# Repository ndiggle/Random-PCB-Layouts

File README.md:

# Random-PCB-Layouts

## Objective
I've uploaded some PCB layouts that I've done in Eagle and KiCad over the past few months. The majority of these layouts were done for pedagogical purposes, but feel free to use any of the designs for alternate uses.

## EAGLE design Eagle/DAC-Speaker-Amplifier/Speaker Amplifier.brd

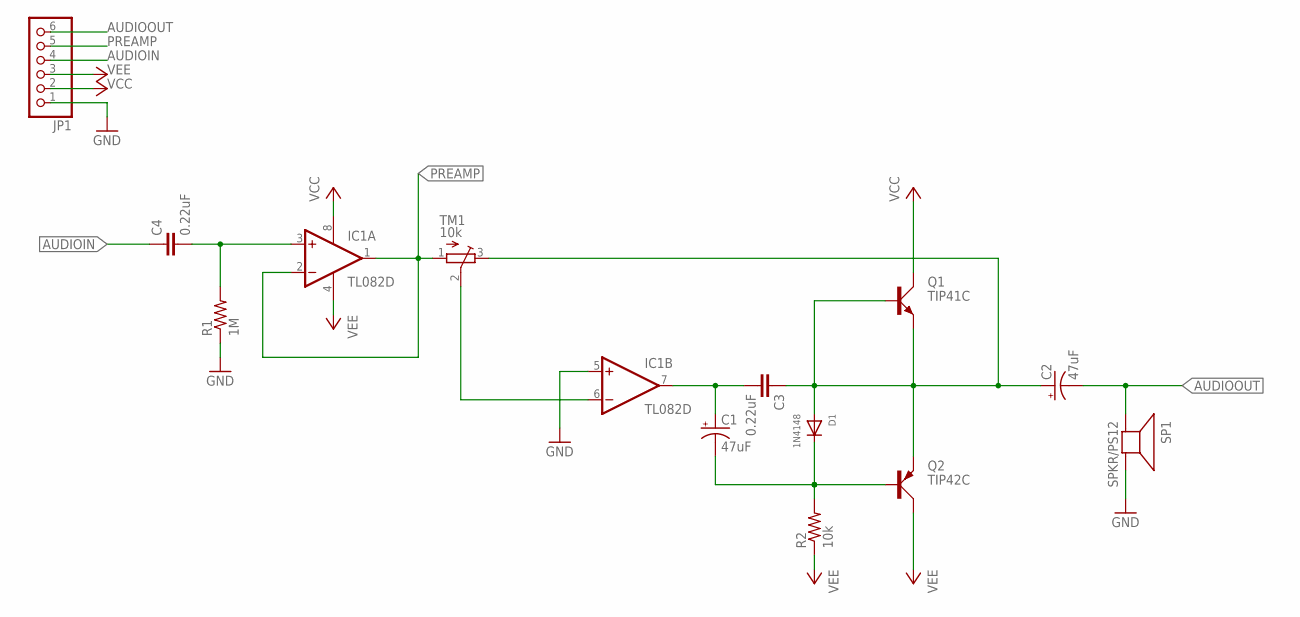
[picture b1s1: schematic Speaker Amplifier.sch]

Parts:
C1, C2: 47uF; 153CLV-0810
C3, C4: 0.22uF; C0805
D1: 1N4148; SOD-323F
IC1: TL082D; SO08
JP1: PINHD-1X6-3.5MM; 1X06-3.5MM
Q1: TIP41C; TO220AV
Q2: TIP42C; TO220AV
R1: 1M; R0805
R2: 10k; R0805
SP1: SPKR/PS12; PS12
TM1: 10k; TC33X

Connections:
AUDIOIN: C4.1, JP1.4
AUDIOOUT: C2.-, JP1.6, SP1.P$1 (+)
GND: IC1.5 (+IN), JP1.1, R1.1, SP1.P$2 (-)
unnamed: C4.2, IC1.3 (+IN), R1.2
unnamed: C1.-, D1.C, Q2.B, R2.2
unnamed: C1.+, C3.2, IC1.7 (OUT)
unnamed: C2.+, C3.1, D1.A, Q1.B, Q1.E, Q2.E, TM1.3 (E)
unnamed: IC1.6 (-IN), TM1.2 (S)
PREAMP: IC1.1 (OUT), IC1.2 (-IN), JP1.5, TM1.1 (A)
VCC: IC1.4 (V-), IC1.8 (V+), JP1.2, JP1.3, Q1.C, Q2.C, R2.1

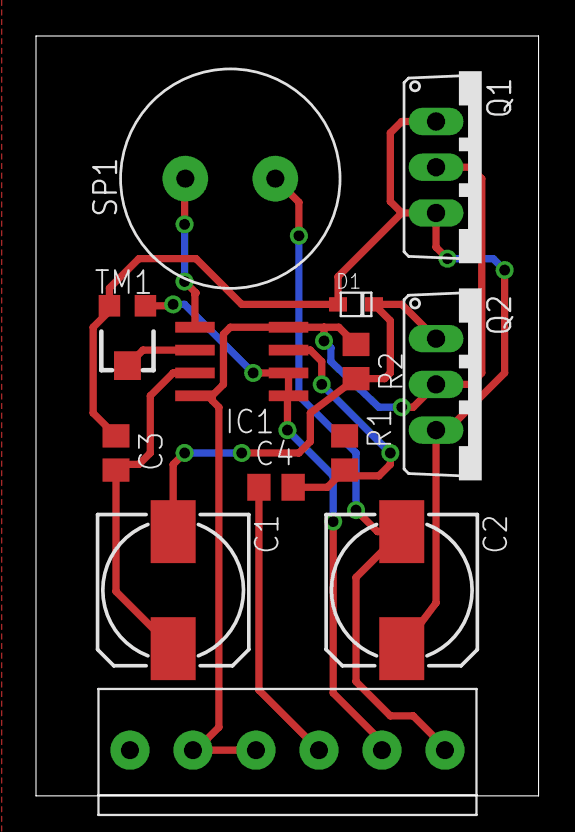
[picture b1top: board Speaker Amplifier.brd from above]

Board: 2 copper layers, 27.9 x 42.2 mm, 13 parts (0 on the bottom side), 10 nets.

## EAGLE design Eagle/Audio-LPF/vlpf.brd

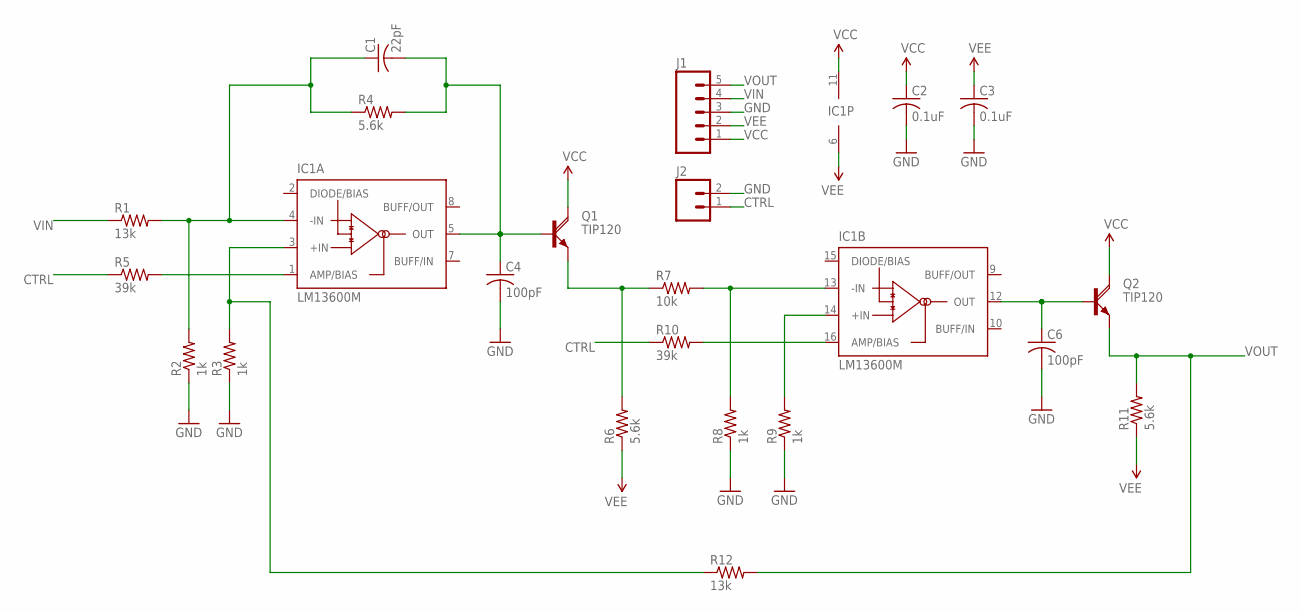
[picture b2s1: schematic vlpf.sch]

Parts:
C1: 22pF; C0504
C2, C3: 0.1uF; C0504
C4, C6: 100pF; C0504
IC1: LM13600M; SO16
J1: M05PTH; 1X05
J2: M02PTH; 1X02
Q1, Q2: TIP120; TO220AH
R1, R12: 13k; R0402
R2, R3, R8, R9: 1k; R0402
R4, R6, R11: 5.6k; R0402
R5, R10: 39k; R0402
R7: 10k; R0402

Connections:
CTRL: J2.1, R5.1, R10.1
GND: C2.2, C3.2, C4.2, C6.2, J1.3, J2.2, R2.1, R3.1, R8.1, R9.1
unnamed: C1.1, IC1.4 (-IN), R1.2, R2.2, R4.1
unnamed: IC1.3 (+IN), R3.2, R12.1
unnamed: C1.2, C4.1, IC1.5 (OUT), Q1.B, R4.2
unnamed: IC1.1 (AMP/BIAS), R5.2
unnamed: Q1.E, R6.2, R7.1
unnamed: IC1.13 (-IN), R7.2, R8.2
unnamed: IC1.14 (+IN), R9.2
unnamed: IC1.16 (AMP/BIAS), R10.2
unnamed: C6.1, IC1.12 (OUT), Q2.B
VCC: C2.1, IC1.11 (V+), J1.1, Q1.C, Q2.C, R6.1, R11.1
VEE: C3.1, IC1.6 (V-), J1.2
VIN: J1.4, R1.1
VOUT: J1.5, Q2.E, R11.2, R12.2

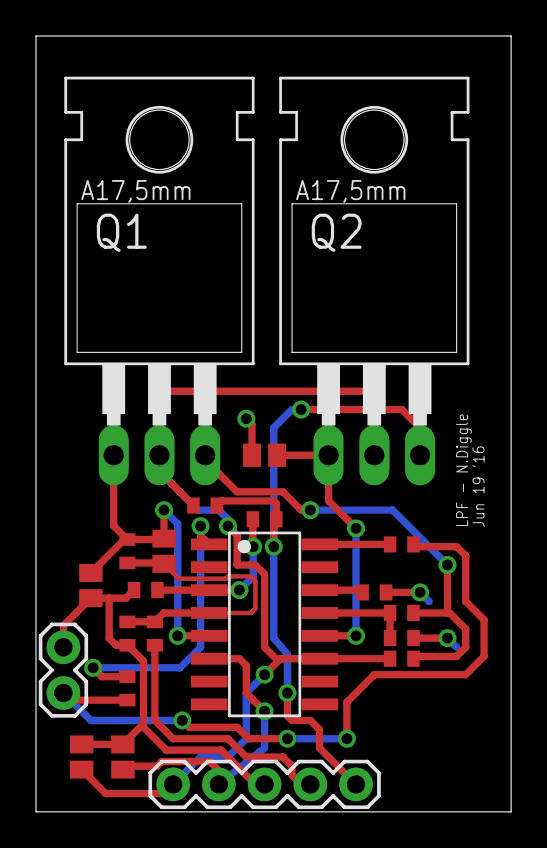
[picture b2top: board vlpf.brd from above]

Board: 2 copper layers, 26.4 x 43.1 mm, 22 parts (0 on the bottom side), 15 nets.

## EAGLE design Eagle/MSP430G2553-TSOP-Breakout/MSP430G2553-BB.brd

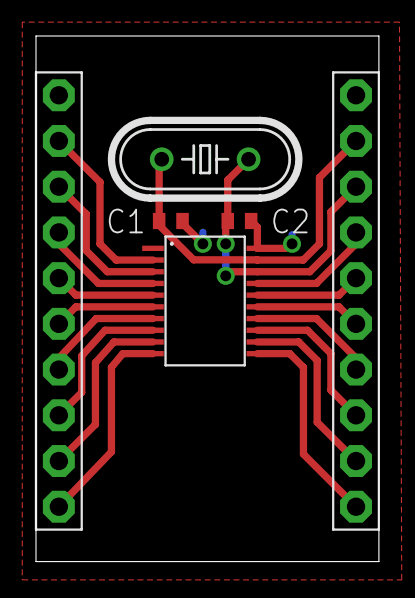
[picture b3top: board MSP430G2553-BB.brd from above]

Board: 2 copper layers, 19.1 x 29.2 mm, 6 parts (0 on the bottom side), 20 nets.

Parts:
C1, C2: C0402
Q1: HC49/S
U$1: G2X[0/3]2---PW20; PW20
U$2, U$3: PINHD-1X10; 1X10-BIG

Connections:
GND: C1.2, C2.2, U$1.20, U$3.10
unnamed: U$1.2, U$2.2
unnamed: U$1.3, U$2.3
unnamed: U$1.4, U$2.4
unnamed: U$1.5, U$2.5
unnamed: U$1.6, U$2.6
unnamed: U$1.7, U$2.7
unnamed: U$1.8, U$2.8
unnamed: U$1.9, U$2.9
unnamed: U$1.10, U$2.10
unnamed: U$1.11, U$3.1
unnamed: U$1.12, U$3.2
unnamed: U$1.13, U$3.3
unnamed: U$1.14, U$3.4
unnamed: U$1.15, U$3.5
unnamed: U$1.16, U$3.6
unnamed: U$1.17, U$3.7
VCC: U$1.1, U$2.1
XIN: C1.1, Q1.1, U$1.19, U$3.9
XOUT: C2.1, Q1.2, U$1.18, U$3.8

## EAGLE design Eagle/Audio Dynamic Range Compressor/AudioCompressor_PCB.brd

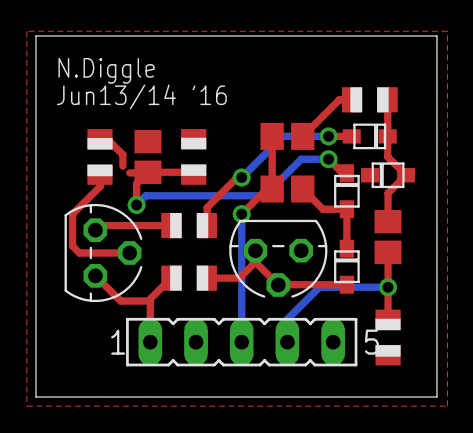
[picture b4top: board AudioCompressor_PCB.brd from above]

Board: 2 copper layers, 22.3 x 20.1 mm, 17 parts (0 on the bottom side), 12 nets.

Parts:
C1, C2: 0.22uF; C0805
C3, C4: 0.47uF; C0805
D1, D2, D3, D4: SOD-323F
R1, R3: 10k; R0805
R2: 100k; R0805
R4: 240k; R0805
R5: 100; R0805
R6: 6.8k; R0805
SV1: FE05-1
T1, T2: 2N3904; TO92

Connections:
GND: C4.2, D4.C, R2.1, R4.1, SV1.2, SV1.5, T1.3
unnamed: C1.2, R1.1
unnamed: C2.1, D3.C, D4.A, R1.2
unnamed: R5.1, T2.2
unnamed: C4.1, D2.C, R4.2
unnamed: R6.2, T2.3
unnamed: D1.A, R3.1, T1.1, T1.2
unnamed: D3.A, R6.1
unnamed: C3.2, D1.C, D2.A
VCC: R3.2, SV1.1, T2.1
VIN: C1.1, C3.1, SV1.3
VOUT: C2.2, R2.2, SV1.4

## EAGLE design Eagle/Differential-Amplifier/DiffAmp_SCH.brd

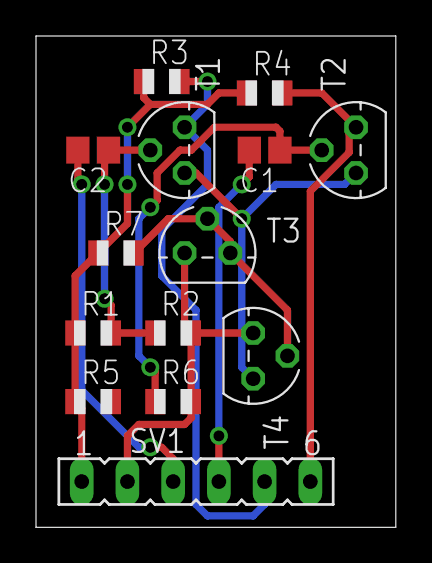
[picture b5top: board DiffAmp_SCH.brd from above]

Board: 2 copper layers, 20.0 x 27.3 mm, 14 parts (0 on the bottom side), 10 nets.

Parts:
C1, C2: C0805
R1, R2, R3, R4, R5, R6, R7: R0805
SV1: FE06
T1, T2, T3, T4: 2N3904; TO92

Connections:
GND: R2.2, R6.2, SV1.2, T3.3, T4.3
unnamed: T1.3, T2.3, T4.1
unnamed: C1.1, R5.2, R6.1, T2.2
unnamed: R7.2, T3.1, T3.2, T4.2
unnamed: C2.1, R1.2, R2.1, T1.2
VCC: R1.1, R3.1, R4.1, R5.1, R7.1, SV1.1
VINN: C1.2, SV1.4
VINP: C2.2, SV1.3
VOUTN: R4.2, SV1.6, T2.1
VOUTP: R3.2, SV1.5, T1.1

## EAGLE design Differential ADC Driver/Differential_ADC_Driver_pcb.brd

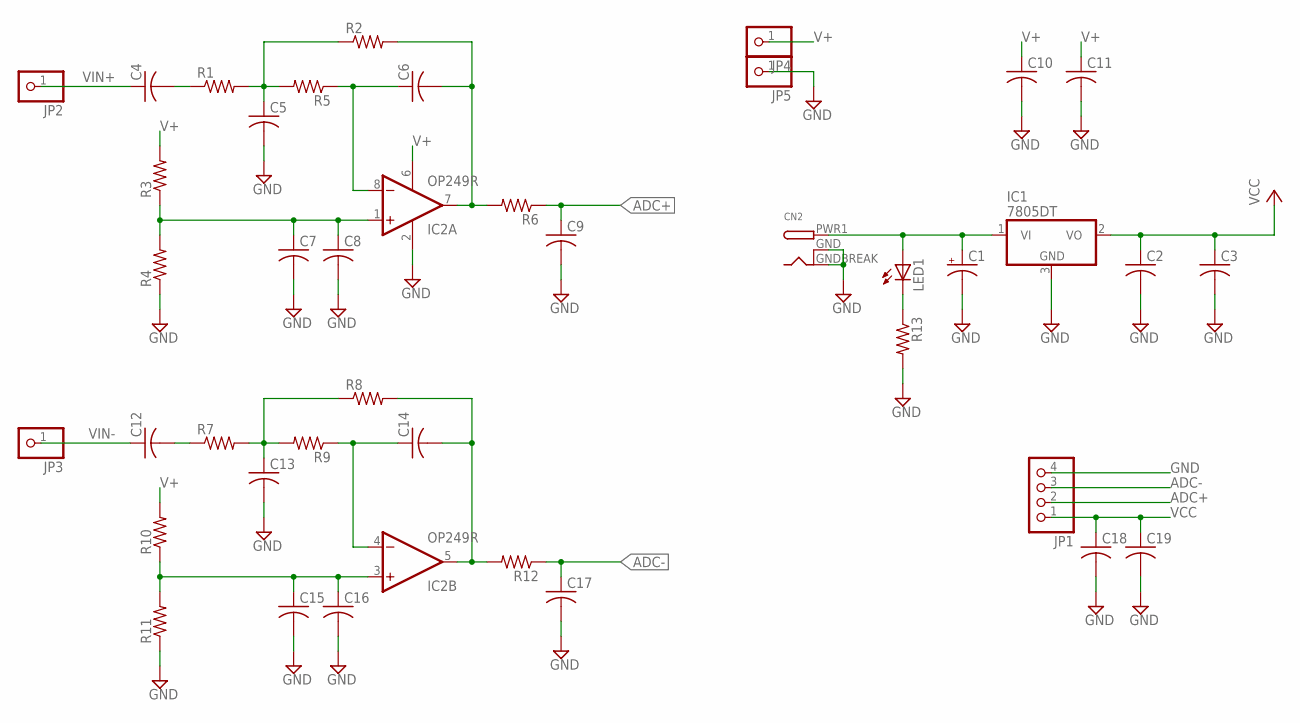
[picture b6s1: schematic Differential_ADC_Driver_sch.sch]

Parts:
C1: CPOL-US153CLV-0405; 153CLV-0405
C2, C3, C18, C19: C-USC0805; C0805
C4, C5, C6, C7, C8, C9, C10, C11, C12, C13, C14, C15, C16, C17: C-USC0402; C0402
CN2: DCBARRELSMT; DCJACK_2MM_SMT
IC1: 7805DT; TO252
IC2: OP249R; SO08
JP1: PINHD-1X4; 1X04
JP2, JP3, JP4, JP5: PINHD-1X1; 1X01
LED1: LEDCHIP-LED0603; CHIP-LED0603
R1, R2, R3, R4, R5, R6, R7, R8, R9, R10, R11, R12, R13: R-US_R0402; R0402

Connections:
ADC+: C9.1, JP1.2, R6.1
ADC-: C17.1, JP1.3, R12.1
GND: C1.-, C2.2, C3.2, C5.2, C7.2, C8.2, C9.2, C10.2, C11.2, C13.2, C15.2, C16.2, C17.2, C18.2, C19.2, CN2.GND (GNDBREAK), CN2.GNDBREAK (GND), IC1.3 (GND), IC2.2 (V-), JP1.4, JP5.1, R4.1, R11.1, R13.2
unnamed: C7.1, C8.1, IC2.1 (+IN), R3.1, R4.2
unnamed: C4.2, R1.1
unnamed: C5.1, R1.2, R2.1, R5.2
unnamed: C6.1, IC2.8 (-IN), R5.1
unnamed: C6.2, IC2.7 (OUT), R2.2, R6.2
unnamed: C12.2, R7.1
unnamed: C13.1, R7.2, R8.1, R9.2
unnamed: C14.1, IC2.4 (-IN), R9.1
unnamed: C14.2, IC2.5 (OUT), R8.2, R12.2
unnamed: C15.1, C16.1, IC2.3 (+IN), R10.1, R11.2
unnamed: LED1.C, R13.1
unnamed: C1.+, CN2.PWR1 (PWR), IC1.1 (VI), LED1.A
V+: C10.1, C11.1, IC2.6 (V+), JP4.1, R3.2, R10.2
VCC: C2.1, C3.1, C18.1, C19.1, IC1.2 (VO), JP1.1
VIN+: C4.1, JP2.1
VIN-: C12.1, JP3.1

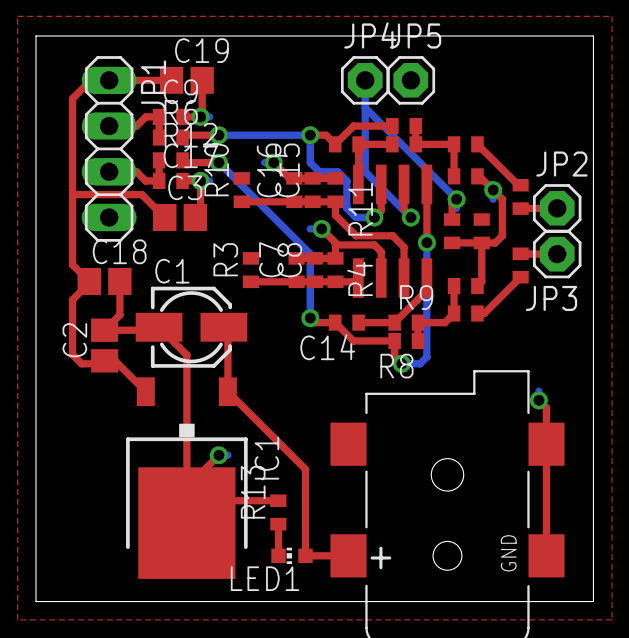
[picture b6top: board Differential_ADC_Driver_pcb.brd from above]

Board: 2 copper layers, 31.0 x 31.4 mm, 41 parts (0 on the bottom side), 19 nets.

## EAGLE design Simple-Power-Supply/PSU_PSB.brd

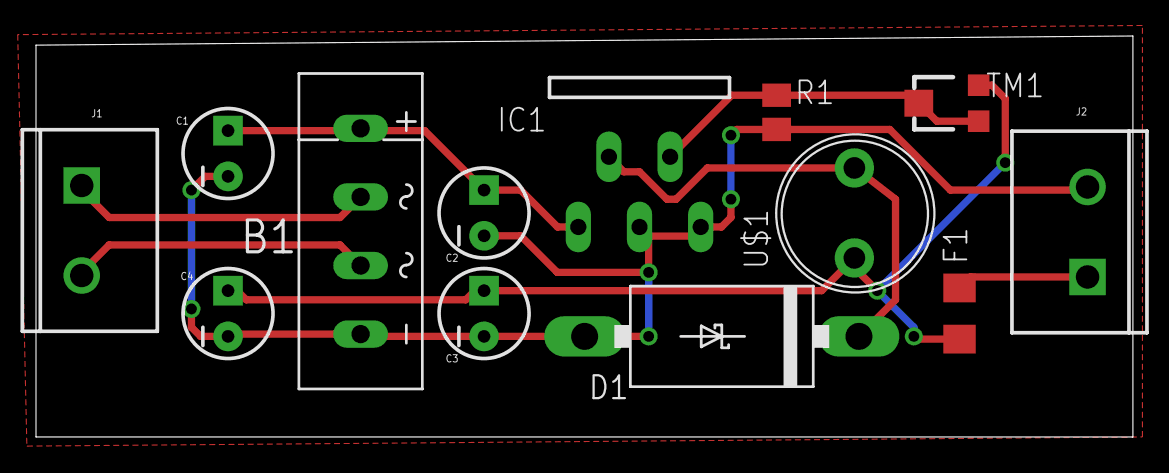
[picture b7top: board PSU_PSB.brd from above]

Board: 2 copper layers, 60.9 x 22.3 mm, 13 parts (0 on the bottom side), 8 nets.

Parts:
B1: 3KBP06M-E4-51; 2KBP
C1: 4700uF; CPOL-RADIAL-10UF-25V
C2, C4: 100uF; CPOL-RADIAL-10UF-25V
C3: 330uF; CPOL-RADIAL-10UF-25V
D1: 1N5822; DO201T15
F1: 0697H2500-01; R1206
IC1: LM2596; TO220-51
J1, J2: SCREWTERMINAL-5MM-2
R1: 1.21k; M0805
TM1: 50k; TC33X
U$1: 300uH; 6000

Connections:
20VACIN: B1.AC1, J1.2
GND: B1.-, C1.2, C2.2, C3.2, C4.2, D1.A, IC1.3, IC1.5, J2.2, R1.1
unnamed: B1.AC2, J1.1
unnamed: B1.+, C1.1, C2.1, IC1.1
unnamed: IC1.4, R1.2, TM1.1, TM1.2
unnamed: D1.C, IC1.2, U$1.1
unnamed: C3.1, C4.1, F1.1, TM1.3, U$1.2
unnamed: F1.2, J2.1

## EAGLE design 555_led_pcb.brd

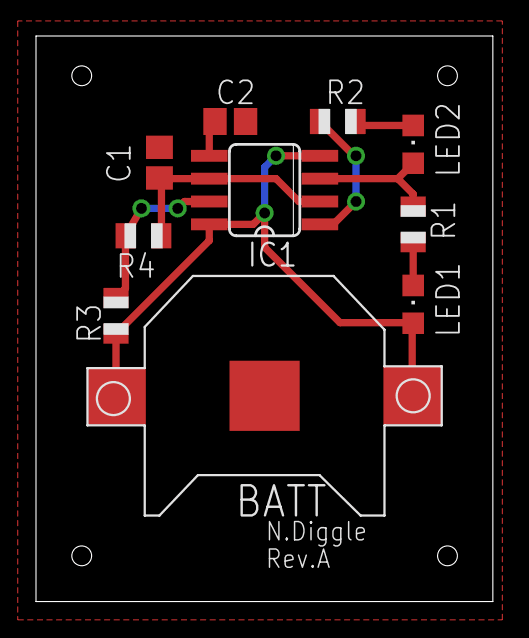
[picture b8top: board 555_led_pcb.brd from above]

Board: 2 copper layers, 25.4 x 31.4 mm, 10 parts (0 on the bottom side), 8 nets.

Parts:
BATT: CR1220; CR1220-SMD
C1: 22uF; C0805
C2: 0.01uF; C0805
IC1: LM555D; SO08
LED1, LED2: Green; CHIPLED_0805
R1, R2: 100; R0805
R3: 1k; R0805
R4: 100k; R0805

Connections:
GND: BATT.-, C1.2, C2.2, IC1.1, R2.1
unnamed: LED1.C, R1.2
unnamed: IC1.3, LED2.A, R1.1
unnamed: LED2.C, R2.2
unnamed: IC1.7, R3.1, R4.2
unnamed: C2.1, IC1.5
NEW1: C1.1, IC1.2, IC1.6, R4.1
VCC: BATT.+$1, BATT.+$2, IC1.4, IC1.8, LED1.A, R3.2

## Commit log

2016-07-29 Rename bbSch1.brd to Buck-Boost-Prototype/bbSch1.brd
2016-07-29 Rename bbSch1.sch to Buck-Boost-Prototype/bbSch1.sch
2016-07-29 Rename headphone_amp.brd to Mini-Headphone-Amplifier/headphone_amp.brd
2016-07-29 Rename headphone_amp.sch to Mini-Headphone-Amplifier/headphone_amp.sch
2016-07-29 Rename vlpf.brd to Audio-LPF/vlpf.brd
2016-07-29 Rename vlpf.sch to Audio-LPF/vlpf.sch
2016-07-29 Rename 555_led_pcb.brd to 555-Blink-Test/555_led_pcb.brd
2016-07-29 Rename 555_led_schematic.sch to 555-Blink-Test/555_led_schematic.sch
2016-07-29 Create tempFile
2016-07-29 Create tempfile
2016-07-31 Added new schematic/PCB for Audio Comrpessor
2016-08-02 Added new sch/pcb
2016-08-19 Added new KiCad layouts
2016-08-19 Sorting out issue with commits
2016-08-19 Deleted the temporary file
2016-08-19 Put all Eagle files into their own directory
2016-08-30 Added datasheet to be used for refference.
2016-09-09 Create Temp
2016-09-26 Added RC car remote sch/pcb
2016-09-26 Reorganized folders and renamed 555 kicad project
2016-09-26 Separated Eagle and Kicad files into seprate folders.

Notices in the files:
parts and their libraries:
SparkFun-Connectors: Licensing: Creative Commons ShareAlike 4.0 International - https://creativecommons.org/licenses/by-sa/4.0
